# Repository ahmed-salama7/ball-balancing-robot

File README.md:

# Real-Time Ball-Balancing Robot

A closed-loop **ball-on-plate** balancing platform. A camera tracks a ball on a circular plate, and a **3-RRS parallel manipulator** driven by three servos tilts the plate to roll the ball back to the center — in real time.

A PC runs the computer-vision pipeline (OpenCV) and streams the ball's pixel coordinates over USB to an **STM32F103C8T6 "Blue Pill"**, which closes the loop with a **PID controller** and an **inverse-kinematics** solver that converts the desired plate tilt into the three servo angles.

---

## Table of Contents

- [How It Works](#how-it-works)
- [Demo & Gallery](#demo--gallery)
- [Repository Structure](#repository-structure)
- [Hardware](#hardware)
  - [Bill of Materials](#bill-of-materials)
  - [Schematic & PCB](#schematic--pcb)
  - [Board Connectors](#board-connectors)
  - [STM32 Pinout](#stm32-pinout)
  - [Power](#power)
  - [KiCad Source](#kicad-source)
- [Mechanical Design](#mechanical-design)
- [Computer Vision](#computer-vision)
- [Control System (PID)](#control-system-pid)
- [Inverse Kinematics](#inverse-kinematics)
- [System Modeling](#system-modeling)
- [Getting Started](#getting-started)
- [Tuning Guide](#tuning-guide)
- [Roadmap](#roadmap)
- [Team](#team)
- [License](#license)

---

## How It Works

The system is a continuous feedback loop running at **50 Hz**:

```mermaid
flowchart LR
    CAM([USB Camera]) --> CV

    subgraph PC["PC — Python / OpenCV"]
        direction TB
        CV["Ball Detection<br/>(HoughCircles)"] --> TX["Serial TX<br/>'x,y' @ 50 Hz"]
    end

    TX -->|"USB CDC<br/>Virtual COM @ 115200"| RX

    subgraph STM["STM32F103C8T6 — Blue Pill"]
        direction TB
        RX["USB CDC RX<br/>parse x,y"] --> PID["PID Controller"]
        PID -->|"tilt slopes (nx, ny)"| IK["Inverse Kinematics<br/>(3-RRS)"]
        IK -->|"θA, θB, θC"| PWM["TIM2 PWM<br/>50 Hz"]
    end

    PWM --> SA([Servo A])
    PWM --> SB([Servo B])
    PWM --> SC([Servo C])

    SA --> PLATE[/Tilting Platform/]
    SB --> PLATE
    SC --> PLATE

    PLATE -.->|"ball rolls toward center"| CAM
```

| Stage | Where | What happens |
|-------|-------|--------------|
| **1. Detect** | PC (Python) | A webcam frame is processed with OpenCV. The ball is found with a Hough circle transform, returning its `(x, y)` pixel position. |
| **2. Transmit** | PC → MCU | The coordinates are sent as an ASCII string `"x,y\n"` over a USB CDC virtual COM port at up to 50 Hz. |
| **3. Compute error** | STM32 | The pixel error is `error = center − ball`, where the center is `(320, 240)`. |
| **4. PID** | STM32 | A discrete PID controller turns the error into a desired **platform tilt slope** `(nx, ny)`, saturated for safety. |
| **5. Inverse kinematics** | STM32 | The tilt slope and platform height are converted into three servo joint angles `(θA, θB, θC)`. |
| **6. Actuate** | STM32 → servos | Angles are mapped to PWM and written to the three servos via TIM2, tilting the plate so the ball rolls back toward center. |

---

## Demo & Gallery

| The finished robot | Assembled controller board |
|:---:|:---:|
|  |  |

| Bench setup | CAD — isometric | CAD — side |
|:---:|:---:|:---:|
|  |  |  |

> A full project presentation (mechanical design, system identification, Simulink models, results) is included at
> [`docs/presentation/Real-Time-Ball-Balancing-Robot.pptx`](docs/presentation/Real-Time-Ball-Balancing-Robot.pptx).

---

## Repository Structure

```
ball-balancing-robot/
├── README.md                     ← you are here
├── LICENSE
├── .gitignore
│
├── vision/                       # PC-side computer vision (Python)
│   ├── ball_tracker.py           # main tracker: detects ball, streams coords over serial
│   ├── circle_calibration.py     # helper to align the camera with the physical plate
│   ├── requirements.txt
│   └── README.md
│
├── firmware/
│   ├── arduino/                  # Reference prototype (Arduino / STM32duino)
│   │   ├── ball_balancer/
│   │   │   ├── ball_balancer.ino # control loop: serial → PID → IK → servos
│   │   │   ├── InverseKinematics.cpp
│   │   │   └── InverseKinematics.h
│   │   └── README.md
│   │
│   └── stm32/                     # Deployed firmware (STM32CubeIDE / HAL)
│       ├── Core/                  # application code (main.c) + HAL init
│       ├── Drivers/               # CMSIS + STM32F1xx HAL drivers
│       ├── Middlewares/           # ST USB Device library
│       ├── USB_DEVICE/            # USB CDC (virtual COM) app layer
│       ├── usb_cdc.ioc            # CubeMX configuration (TIM2 PWM + USB CDC)
│       ├── STM32F103C8TX_FLASH.ld
│       ├── .cproject / .project / .mxproject
│       └── README.md
│
├── hardware/
│   ├── README.md                 # PCB, power, wiring notes
│   └── kicad/                     # editable KiCad PCB source (open the .kicad_pro)
│       ├── <project>.kicad_pro   #   project file
│       ├── <project>.kicad_sch   #   schematic
│       ├── <project>.kicad_pcb   #   board layout
│       └── <project>.kicad_prl   #   local settings
│
└── docs/
    ├── images/                   # photos, CAD renders, schematic, PCB
    └── presentation/             # full project slide deck (.pptx)
```

---

## Hardware

### Bill of Materials

| Qty | Component | Notes |
|:---:|-----------|-------|
| 1 | **STM32F103C8T6 "Blue Pill"** | Main controller. 72 MHz Cortex-M3. |
| 3 | **9g micro servos** | Drive the three RRS legs (e.g. SG90 / MG90S class). |
| 1 | **ST-Link V2** | For flashing & SWD debugging the Blue Pill. |
| 1 | **USB webcam** | Mounted above the plate, looking straight down. |
| 1 | **External 5 V power adapter** | Powers the servos (do **not** power servos from the Blue Pill's regulator). |
| 1 | **Custom PCB** | Routes signals and 5 V power to the servos (KiCad design). |
| 1 | **Circular plate + ball** | Flat plate where the ball rolls (a standard ping-pong ball). |
| 1 | **Perfboard / protoboard** | The final build hand-wires the Blue Pill and servo headers on perfboard (see note below). |
| — | **3D-printed parts** | Base, legs, servo horns, platform mounts. |

### Schematic & PCB

| Schematic | PCB layout | PCB 3D render |
|:---:|:---:|:---:|
|  |  |  |

The custom PCB acts as a carrier/breakout for the Blue Pill (`J1`, `J2`), the servo headers (`M1`–`M3`), the ST-Link SWD header (`J4`), and an auxiliary header (`J5`), with the servo signal lines and a shared external 5 V/GND rail.

> **Design vs. build.** The board above is the **KiCad design**. The **final working build** uses an STM32 Blue Pill hand-soldered onto perfboard with jumper wires out to the three servos and the ST-Link — the images below. The pin assignments are identical; only the physical routing differs.
>
> <p align="center">
>   
> </p>

### Board Connectors

The board is a carrier/breakout that fans the Blue Pill out to the three servos and the ST-Link, distributing the external 5 V servo power and a common ground.

| Ref | Role |
|-----|------|
| `J1`, `J2` | Blue Pill headers (2× 20-pin) that carry the MCU onto the board. |
| `M1`, `M2`, `M3` | Servo connectors (signal / +5 V / GND) for legs A, B, C. |
| `J4` | ST-Link V2 SWD header (SWDIO, SWCLK, 3V3, GND). |
| `J5` | Auxiliary header. |
| `C1`–`C3` | Decoupling for the servo power rail. |

### STM32 Pinout

The firmware uses **TIM2** for three hardware-PWM servo channels and the on-chip **USB peripheral** as a CDC virtual COM port.

| Pin | Peripheral / Function | Connected to |
|-----|-----------------------|--------------|
| **PA0** | `TIM2_CH1` — PWM | Servo **A** (Leg A / M1) signal |
| **PA1** | `TIM2_CH2` — PWM | Servo **B** (Leg B / M2) signal |
| **PA3** | `TIM2_CH4` — PWM | Servo **C** (Leg C / M3) signal |
| **PA11** | `USB_DM` | USB D− → PC |
| **PA12** | `USB_DP` | USB D+ → PC |
| **PA13** | `SWDIO` | ST-Link V2 |
| **PA14** | `SWCLK` | ST-Link V2 |
| **PC13** | GPIO output | On-board LED |
| **5V (ext.)** | Power | Servo VCC (external 5 V adapter) |
| **GND** | Ground | Common ground (PC, MCU, servos) |

**PWM timing.** TIM2 is clocked so that one count = 1 µs (`Prescaler = 72−1`) with a period of 20,000 counts (`Period = 20000−1`) → a **20 ms / 50 Hz** servo frame. Pulse widths in the ~1000–2000 µs range set servo position.

> **Note on pin numbering.** The KiCad schematic labels the servos on PA0/PA1/**PA2**, while the shipped CubeMX configuration drives them on PA0/PA1/**PA3** (TIM2 channels 1, 2, 4). The firmware is the source of truth — use **PA0 / PA1 / PA3**.

### Power

> ⚠️ **Never** power the servos from the Blue Pill's on-board regulator — three servos under load can momentarily draw amps and will brown out the MCU.

- Use a dedicated **5 V adapter** sized for your servos.
- Tie **all grounds together** — PC USB ground, MCU ground, and the servo-supply ground — so the PWM signals share a common reference.

### KiCad Source

The board's editable source lives in [`hardware/kicad/`](hardware/kicad/):

| File | What it is |
|------|-----------|
| `*.kicad_pro` | KiCad project file — open this one. |
| `*.kicad_sch` | Schematic. |
| `*.kicad_pcb` | PCB layout. |
| `*.kicad_prl` | Project-local settings. |

Open the `.kicad_pro` in **KiCad 7 or later** to view or edit the schematic and board, or to export gerbers for fabrication. Auto-generated backups, autosaves, and caches are excluded by `.gitignore`.

---

## Mechanical Design

The platform is a **3-RRS parallel manipulator** (each leg: a base **R**evolute joint actuated by a servo → a link → a **S**pherical joint at the moving plate; "RRS" denotes the joint chain per leg). Three legs spaced 120° apart give the plate the two tilt degrees of freedom needed to steer the ball, plus a controllable height.

The inverse-kinematics solver is parameterized by four lengths (all in **centimeters**), set in the firmware:

| Symbol | Meaning | Value (cm) |
|:------:|---------|:----------:|
| `d` | Base center → corner distance | 5.70 |
| `e` | Platform center → corner distance | 8.50 |
| `f` | Link 1 length (servo horn) | 3.10 |
| `g` | Link 2 length (connecting rod) | 9.66 |
| `hz` | Baseline platform height | 10.25 |

**Servo calibration** (neutral angle = plate level), from the firmware:

| | Leg A | Leg B | Leg C |
|---|:---:|:---:|:---:|
| Neutral angle | 74° | 97° | 83° |
| Direction sign | +1 | +1 | +1 |
| Safe travel limits | \[40°, 100°\] | \[40°, 100°\] | \[40°, 100°\] |

> Design goals: a stiff plate, **known neutral geometry** so the IK baseline is exact, and conservative servo travel limits so the mechanism can never drive itself into a hard stop.

---

## Computer Vision

The vision script ([`vision/ball_tracker.py`](vision/ball_tracker.py)) detects the ball and streams its position. The pipeline:

1. **Pre-process** — convert the frame to grayscale and apply a 9×9 Gaussian blur to suppress noise.
2. **Detect** — run a Hough circle transform (`cv2.HoughCircles`) to find circular candidates within a radius band.
3. **Validate** — for the white ball, the mean brightness *inside* each candidate circle is checked, rejecting non-ball circles. _(An alternative HSV color-threshold path can be used for a colored ball — see the slide deck.)_
4. **Overlay & calibrate** — a fixed reference circle is drawn at the image center `(320, 240)` so the camera frame can be physically aligned with the plate. Use [`circle_calibration.py`](vision/circle_calibration.py) to do this alignment.
5. **Transmit** — when the ball is found, the script sends `"x,y\n"` over the serial port (`COM11` @ 115200 by default). A status overlay shows the live connection state and detected pixel coordinates.

> **Set your serial port** at the top of `ball_tracker.py` (`serial_port = "COM11"`). On Linux/macOS this looks like `/dev/ttyACM0` or `/dev/tty.usbmodemXXXX`.

---

## Control System (PID)

The controller runs on a fixed sample time of $\Delta t = 20\ \text{ms}$ (50 Hz). The error is the offset of the ball from the image center, computed independently on each axis:

$$
e_x = c_x - b_x, \qquad e_y = c_y - b_y
$$

where $(c_x, c_y) = (320, 240)$ px is the target center and $(b_x, b_y)$ is the detected ball position.

A discrete PID is evaluated per axis, using **trapezoidal integration**:

$$
I_k = I_{k-1} + \left(e_k + e_{k-1}\right)\,\Delta t
$$

$$
D_k = \frac{e_k - e_{k-1}}{\Delta t}
$$

$$
u_k = K_p\, e_k + K_i\, I_k + K_d\, D_k
$$

The output $u_k$ is the **commanded plate tilt slope** $(n_x, n_y)$, clamped to a safe range to bound how far the plate can tilt:

$$
u_k \in \left[-s_{\max},\ +s_{\max}\right], \qquad s_{\max} = 0.6
$$

If no fresh coordinate arrives within ~500 ms, the controller commands the plate flat as a failsafe.

**Gains.** The PID gains were tuned iteratively; the value of starting from a small proportional gain and adding derivative damping is documented inline in the firmware. They are exposed as plain constants (`kp`, `ki`, `kd`) so you can re-tune for your own servos, plate friction, and camera latency — see the [Tuning Guide](#tuning-guide).

---

## Inverse Kinematics

Inverse kinematics converts the **desired plate pose** — a unit normal vector $\hat{n} = (n_x, n_y, n_z)$ and a height $h_z$ — into the **servo angle required for each leg**.

For each leg the solver evaluates a closed-form expression (derived from the leg geometry $d, e, f, g$) and returns the joint angle $\theta$:

$$
\theta_{\text{leg}} = \texttt{machine.theta}(\text{leg},\ h_z,\ n_x,\ n_y)
$$

The geometric angle is then mapped to a servo command using the per-leg neutral and direction calibration:

$$
\theta_{\text{servo}} = \theta_{\text{neutral}} + s \cdot \mathrm{round}\!\left(\theta - \theta_0\right)
$$

where $\theta_0$ is the baseline angle for a perfectly level plate (computed once at startup) and $s \in \{-1, +1\}$ sets the rotation direction. Each result is finally constrained to the safe travel limits before being written to the servo.

**End-to-end signal flow:**

$$
\underbrace{(b_x, b_y)}_{\text{pixels}} \;\xrightarrow{\text{PID}}\; \underbrace{(n_x, n_y)}_{\text{tilt slopes}} \;\xrightarrow{\text{IK}}\; \underbrace{(\theta_A, \theta_B, \theta_C)}_{\text{joint angles}} \;\xrightarrow{\text{map + PWM}}\; \text{servos}
$$

The full derivation lives in [`InverseKinematics.cpp`](firmware/arduino/ball_balancer/InverseKinematics.cpp).

---

## System Modeling

Beyond hand-tuning, the servos were characterized to enable model-based control design (see the slide deck for figures):

- **Data collection** — the servo's built-in position feedback was logged as `(time [ms], commanded angle [deg], measured angle [deg])`.
- **System identification** — a black-box fit produced a transfer function (settling-time / `Ts`) model of the servo response.
- **Simulink** — the closed loop was modeled both *without* and *with* the inverse-kinematics block, and the step responses were compared against the physical system.

---

## Getting Started

### 1. Vision (PC)

```bash
cd vision
pip install -r requirements.txt
# Edit ball_tracker.py and set serial_port to your board's COM/tty port
python ball_tracker.py
```

A window opens showing the camera feed, the reference circle, the detection, and an `STM: Connected/Disconnected` overlay. Press **`q`** or **`Esc`** to quit. Use `circle_calibration.py` first if you need to physically align the camera with the plate.

### 2. Firmware — STM32 (recommended / deployed)

1. Open **STM32CubeIDE** → *File ▸ Open Projects from File System…* → select `firmware/stm32/`.
2. (Optional) Open `usb_cdc.ioc` in CubeMX to review the TIM2 + USB CDC configuration.
3. Build, connect the **ST-Link V2** to the SWD header, and flash.
4. The board enumerates as a USB **Virtual COM Port** — note the port number and put it in `ball_tracker.py`.

> ⚠️ **Before this builds**, the generated source folders (`Core/`, `Drivers/`, `Middlewares/`, `USB_DEVICE/`) must be present. See **[`firmware/stm32/README.md`](firmware/stm32/README.md)** — those folders are *not* committed here yet, and the README explains exactly how to add them.

### 3. Firmware — Arduino (reference prototype)

```text
Open firmware/arduino/ball_balancer/ball_balancer.ino in the Arduino IDE
→ install the Servo library
→ select your board, then upload
```

This sketch contains the same control logic (PID + inverse kinematics) and is the easiest way to read and understand the algorithm. See [`firmware/arduino/README.md`](firmware/arduino/README.md).

---

## Tuning Guide

Re-tune for your own hardware in this order:

1. **Camera alignment & center.** Run `circle_calibration.py`. Make sure the reference circle is concentric with the plate and `(320, 240)` is the true target. A miscalibrated center is the #1 cause of a ball that "parks" off-center.
2. **Servo neutrals.** With the plate empty, adjust `servoNeutralA/B/C` until the plate is dead level. The IK baseline depends on this.
3. **Proportional gain `kp`.** Start small. Increase until the ball is actively pushed toward center, then back off just before it oscillates.
4. **Derivative gain `kd`.** Add a little to damp overshoot and settle the ball faster.
5. **Integral gain `ki`.** Add a *very* small amount only if the ball consistently settles slightly off-center. Too much integral causes slow oscillation/wind-up.
6. **Safety.** Keep `maxSlope` and the servo travel limits conservative until the loop is stable.

---

## Roadmap

Ideas for extending the project:

- [ ] Trajectory tracking (drive the ball along a circle/figure-8, not just to center)
- [ ] On-board vision (move detection to an MCU/SBC to remove the PC)
- [ ] Auto-tuning or model-based (LQR/state-feedback) control using the identified servo model
- [ ] Latency compensation / ball-velocity estimation (Kalman filter)
- [ ] Publish the KiCad source and 3D-printable STL files

---

## Team

**Team 11**

| Discipline | Member(s) |
|------------|-----------|
| Control | Mohamed Haroun, Abdulrahman Alabed |
| Computer Vision | Taqi Aldeen |
| Electronics | Ahmed Salama |
| Mechanical | Salah Hamwi |
| Embedded Systems | Abdelaziz Hassan |

---

## License

Released under the **MIT License** — see [`LICENSE`](LICENSE).

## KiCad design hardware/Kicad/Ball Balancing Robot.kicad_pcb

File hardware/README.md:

# Hardware

The custom PCB and wiring for the ball-balancing platform.

| Schematic | PCB layout | 3D render |
|:---:|:---:|:---:|
| [`schematic.png`](../docs/images/schematic.png) | [`pcb-layout.png`](../docs/images/pcb-layout.png) | [`pcb-3d.png`](../docs/images/pcb-3d.png) |

> **Design vs. build.** The KiCad board above is the *design*. The **final working build** hand-wires an STM32 Blue Pill on perfboard with jumper wires to the servos and ST-Link (same pin assignments, different physical routing):
>
> 

## What the board does

The PCB is a carrier/breakout that connects the Blue Pill to the three servos and the ST-Link, distributing the external 5 V servo power and a common ground.

| Ref | Role |
|-----|------|
| `J1`, `J2` | Blue Pill headers (2× 20-pin), carrying the MCU into the board. |
| `M1`, `M2`, `M3` | Servo connectors (signal / +5 V / GND) for legs A, B, C. |
| `J4` | ST-Link V2 SWD header (SWDIO, SWCLK, 3V3, GND). |
| `J5` | Auxiliary header. |
| `C1`–`C3` | Decoupling for the servo power rail. |

## Connections at a glance

| Signal | STM32 pin | Goes to |
|--------|-----------|---------|
| Servo A PWM | PA0 (TIM2_CH1) | `M1` signal |
| Servo B PWM | PA1 (TIM2_CH2) | `M2` signal |
| Servo C PWM | PA3 (TIM2_CH4) | `M3` signal |
| SWD | PA13 / PA14 | `J4` (ST-Link) |
| USB | PA11 / PA12 | Blue Pill USB → PC |
| Servo power | — | External **5 V** adapter → `M1/M2/M3` V+ |
| Ground | GND | Common to MCU, servos, and adapter |

> See the main [README pinout note](../README.md#stm32-pinout): the schematic labels servos on PA0/PA1/**PA2**, but the firmware drives PA0/PA1/**PA3**. Follow the firmware.

## ⚠️ Power

- **Never** power the servos from the Blue Pill's on-board regulator — three servos under load can momentarily draw amps and will brown out the MCU.
- Use a dedicated **5 V adapter** sized for your servos, and tie all grounds together (PC USB ground, MCU ground, servo-supply ground).

## To add

The KiCad source (`.kicad_pro`, `.kicad_sch`, `.kicad_pcb`) and any gerbers are not yet committed. Drop them in this folder so others can fabricate or modify the board.

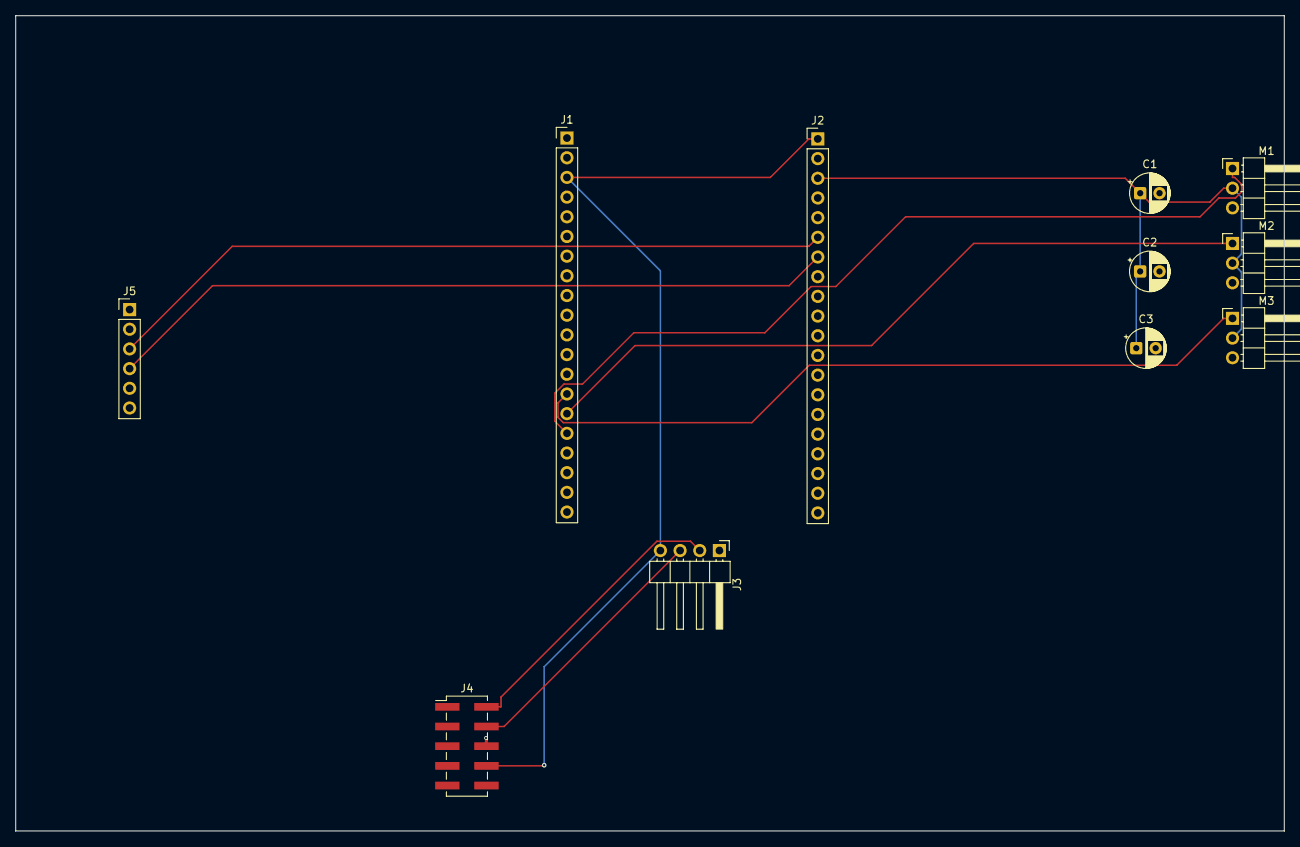
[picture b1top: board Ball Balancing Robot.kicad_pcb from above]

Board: 2 copper layers, 163.7 x 105.2 mm, 11 parts (0 on the bottom side), 10 nets.

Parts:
C1, C2, C3: C; CP_Radial_D5.0mm_P2.50mm
J1, J2: Conn_01x20_Pin; PinHeader_1x20_P2.54mm_Vertical
J3: Conn_01x04_Pin; PinHeader_1x04_P2.54mm_Horizontal
J4: Conn_02x05_Odd_Even; PinHeader_2x05_P2.54mm_Vertical_SMD
J5: Conn_01x06_Pin; PinHeader_1x06_P2.54mm_Vertical
M1, M2, M3: Motor_Servo; PinHeader_1x03_P2.54mm_Horizontal

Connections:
3V3: J1.3, J2.1, J3.4, J4.8
5V: C1.1, C2.1, C3.1, J2.3, M1.2 (+), M2.2 (+), M3.2 (+)
GND: C1.2, C2.2, C3.2, J1.1, J1.2, J2.2, J3.1, J4.6, J5.5, M1.3 (-), M2.3 (-), M3.3 (-)
PA0: J1.16, M1.1 (PWM)
PA1: J1.15, M2.1 (PWM)
PA2: J1.14, M3.1 (PWM)
RXD: J2.6, J5.3
SWCLK: J3.2, J4.2
SWDIO: J3.3, J4.4
TXD: J2.7, J5.4
